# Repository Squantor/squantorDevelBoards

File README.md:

# Various development boards
This project contains a bunch of various development boards I use in my projects. They are usually focused on learning how to use a specific type of microcontroller or application.
## Nuclone development board series
As the name implies they resemble the [ST nucleo](https://www.st.com/en/evaluation-tools/stm32-nucleo-boards.html) in shape and function, minimal evaluation boards with all pins broken out and lot of jumpers.
## Structure
* [electronics](electronics/) contains the various nuclone examples, they are mostly [LPC microcontrollers](https://www.nxp.com/products/processors-and-microcontrollers/arm-microcontrollers/general-purpose-mcus:GENERAL-PURPOSE-MCUS) from [NXP](https://www.nxp.com/) but a few STM32's, nordic and holtek ARM microcontrollers are planned too.
* [software](software/) some example projects or project templates
* [mechanical](mechanical/) contains drawings for project boxes of the nuclone boards
## Checking out
This project makes extensive use of submodules, use ```git clone --recurse-submodules https://github.com/Squantor/squantorDevelBoards.git``` to clone the repository and its submodules in one go.

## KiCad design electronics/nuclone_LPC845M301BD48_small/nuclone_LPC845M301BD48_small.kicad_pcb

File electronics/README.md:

# Development board electronics
Stored here is the electronics for various development boards I use. Most are based on the "nuclone" principle. They look a lot like the STM32 nucleo series development boards.
## List of boards
* [nuclone board for the LPC804M101JHI33](nuclone_LPC804M101JHI33/README.md) is a breakout for the LPC804M101JHI33 microcontroller.
* [nuclone board for the LPC812M101JDH20](nuclone_LPC812M101JDH20/README.md) is a breakout for the LPC812M101JDH20 microcontroller.
* [nuclone board for the LPC824M201JDH20](nuclone_LPC824M201JDH20/README.md) is a breakout for the LPC824M201JDH20 microcontroller.
* [nuclone board for the LPC824M201JHI33](nuclone_LPC824M201JHI33/README.md) is a breakout for the LPC824M201JHI33 microcontroller.
* [nuclone board for the LPC844M201BD64](nuclone_LPC844M201BD64/README.md) is a breakout for the LPC844M201BD64 microcontroller.
* [nuclone board for the LPC845M301JBD48](nuclone_LPC845M301JBD48/README.md) is a breakout for the LPC845M301JBD48 microcontroller.
* [nuclone board for the LPC1114JBD48](nuclone_LPC1114JBD48/README.md) is a breakout for the LPC1114JBD48 microcontroller.
* [nuclone board for the LPC1125JBD48](nuclone_LPC1125JBD48/README.md) is a breakout for the LPC1125JBD48 microcontroller.
* [nuclone board for the STM32F030C8T6](nuclone_STM32F030C8T6/README.md) is a breakout for the STM32F030C8T6 microcontroller.
* [nuclone board for the STM32F030K6](nuclone_STM32F030K6/README.md) is a breakout for the STM32F030K6 microcontroller.
* [nuclone board for the STM32F031K6](nuclone_STM32F031K6/README.md) is a breakout for the STM32F031K6 microcontroller.
* [small nuclone universal expansion board with USB to UART and prototyping area](nuclone_small_uart_expansion/README.md).
* [LPC824M201JHI33 nuclone expansion board with SD card slot](nuclone_LPC824M201JHI33_expansion_microSD_card/README.md).
* [LPC824M201JHI33 nuclone expansion board with SOIC NOR Flash](nuclone_LPC824M201JHI33_expansion_serial_flash_SOIC/README.md).
* [LPC824M201JHI33 nuclone expansion board with USON NOR Flash](nuclone_LPC824M201JHI33_expansion_serial_flash_USON/README.md).
* [LPC824M201JHI33 nuclone expansion board with wearable prototyping circuit](nuclone_LPC824M201JHI33_expansion_wearable/README.md). This contains a battery charger, serial flash for datalogging, usb connection for data download and a few sensors like accelerometer, ambient light and a few more. (WIP)

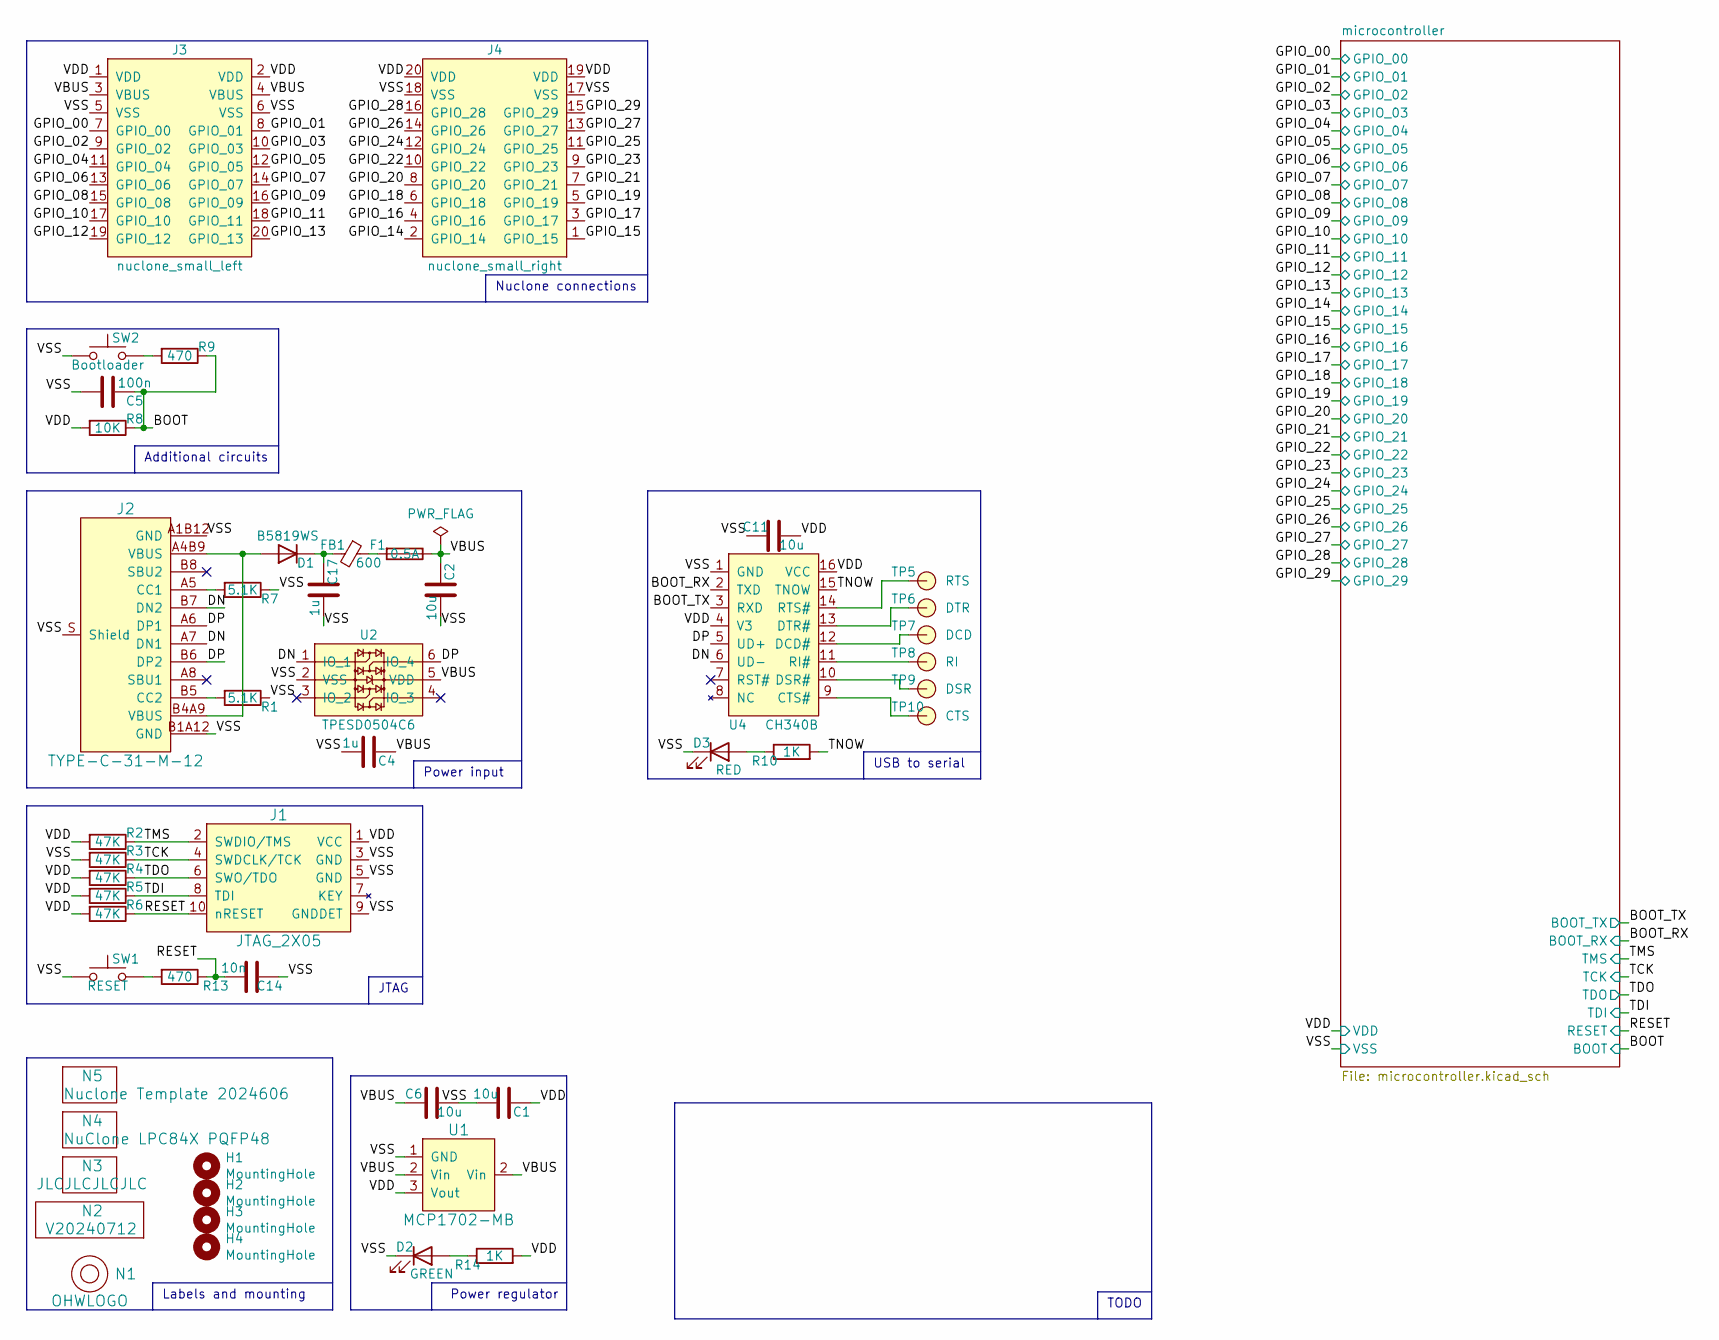
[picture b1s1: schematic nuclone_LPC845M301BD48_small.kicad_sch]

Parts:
C1, C2, C6, C11: 10u; C_0603
C4, C17: 1u; C_0603
C5: 100n; C_0603
C14: 10n; C_0603
D1: B5819WS; SOD-323-nexperia-hand
D2: GREEN; LED_0603_hand
D3: RED; LED_0603_hand
F1: 0.5A; F_0603_hand
FB1: 600; L_0603
H1, H2, H3, H4: MountingHole; MountingHole_3.2mm_M3_Pad_Via
J1: JTAG_2X05; Header-0127-2X05-H006
J2: TYPE-C-31-M-12; USB-C-HRO-31-M-12
J3: nuclone_small_left; nuclone_small_left_stacked
J4: nuclone_small_right; nuclone_small_right_stacked
N1: OHWLOGO; OSHW-Symbol_6.7x6mm_SilkScreen
N2: V20240712; Label_Generic
N3: JLCJLCJLCJLC; Label_Generic
N4: NuClone LPC84X PQFP48; Label_Generic
N5: Nuclone Template 2024606; Label_Generic
R1, R7: 5.1K; R_0603_hand
R2, R3, R4, R5, R6: 47K; R_0603_hand
R8: 10K; R_0603_hand
R9, R13: 470; R_0603_hand
R10, R14: 1K; R_0603_hand
SW1: RESET; TD-85XU
SW2: Bootloader; TD-85XU
TP5: RTS; TestPoint_hole_H05R10
TP6: DTR; TestPoint_hole_H05R10
TP7: DCD; TestPoint_hole_H05R10
TP8: RI; TestPoint_hole_H05R10
TP9: DSR; TestPoint_hole_H05R10
TP10: CTS; TestPoint_hole_H05R10
U1: MCP1702-MB; SOT89-NXP
U2: TPESD0504C6; SOT363-ONsemi
U4: CH340B; SOIC-16_3.9x9.9mm_P1.27mm

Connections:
/BOOT: C5.1, R8.1, R9.1; also elsewhere on the board
/BOOT_RX: U4.2 (TXD); also elsewhere on the board
/BOOT_TX: U4.3 (RXD); also elsewhere on the board
/DN: J2.A7 (DN1), J2.B7 (DN2), U2.1 (IO_1), U4.6 (UD-)
/DP: J2.A6 (DP1), J2.B6 (DP2), U2.6 (IO_4), U4.5 (UD+)
/GPIO_00: J3.7 (GPIO_00); also elsewhere on the board
/GPIO_01: J3.8 (GPIO_01); also elsewhere on the board
/GPIO_02: J3.9 (GPIO_02); also elsewhere on the board
/GPIO_03: J3.10 (GPIO_03); also elsewhere on the board
/GPIO_04: J3.11 (GPIO_04); also elsewhere on the board
/GPIO_05: J3.12 (GPIO_05); also elsewhere on the board
/GPIO_06: J3.13 (GPIO_06); also elsewhere on the board
/GPIO_07: J3.14 (GPIO_07); also elsewhere on the board
/GPIO_08: J3.15 (GPIO_08); also elsewhere on the board
/GPIO_09: J3.16 (GPIO_09); also elsewhere on the board
/GPIO_10: J3.17 (GPIO_10); also elsewhere on the board
/GPIO_11: J3.18 (GPIO_11); also elsewhere on the board
/GPIO_12: J3.19 (GPIO_12); also elsewhere on the board
/GPIO_13: J3.20 (GPIO_13); also elsewhere on the board
/GPIO_14: J4.2 (GPIO_14); also elsewhere on the board
/GPIO_15: J4.1 (GPIO_15); also elsewhere on the board
/GPIO_16: J4.4 (GPIO_16); also elsewhere on the board
/GPIO_17: J4.3 (GPIO_17); also elsewhere on the board
/GPIO_18: J4.6 (GPIO_18); also elsewhere on the board
/GPIO_19: J4.5 (GPIO_19); also elsewhere on the board
/GPIO_20: J4.8 (GPIO_20); also elsewhere on the board
/GPIO_21: J4.7 (GPIO_21); also elsewhere on the board
/GPIO_22: J4.10 (GPIO_22); also elsewhere on the board
/GPIO_23: J4.9 (GPIO_23); also elsewhere on the board
/GPIO_24: J4.12 (GPIO_24); also elsewhere on the board
/GPIO_25: J4.11 (GPIO_25); also elsewhere on the board
/GPIO_26: J4.14 (GPIO_26); also elsewhere on the board
/GPIO_27: J4.13 (GPIO_27); also elsewhere on the board
/GPIO_28: J4.16 (GPIO_28); also elsewhere on the board
/GPIO_29: J4.15 (GPIO_29); also elsewhere on the board
/RESET: C14.2, J1.10 (nRESET), R6.1, R13.1; also elsewhere on the board
/TCK: J1.4 (SWDCLK/TCK), R3.1; also elsewhere on the board
/TDI: J1.8 (TDI), R5.1
/TDO: J1.6 (SWO/TDO), R4.1
/TMS: J1.2 (SWDIO/TMS), R2.1; also elsewhere on the board
/TNOW: R10.2, U4.15 (TNOW)
/VBUS: C2.2, C4.1, C6.1, F1.1, J3.3 (VBUS), J3.4 (VBUS), U1.2 (Vin), U2.5 (VDD)
/VDD: C1.1, C11.1, J1.1 (VCC), J3.1 (VDD), J3.2 (VDD), J4.19 (VDD), J4.20 (VDD), R2.2, R4.2, R5.2, R6.2, R8.2, R14.2, U1.3 (Vout), U4.4 (V3), U4.16 (VCC); also elsewhere on the board
/VSS: C1.2, C2.1, C4.2, C5.2, C6.2, C11.2, C14.1, C17.1, D2.1 (K), D3.1 (K), J1.3 (GND), J1.5 (GND), J1.9 (GNDDET), J2.A1B12 (GND), J2.B1A12 (GND), J2.S (Shield), J3.5 (VSS), J3.6 (VSS), J4.17 (VSS), J4.18 (VSS), R1.1, R3.2, R7.1, SW1.1, SW2.1, U1.1 (GND), U2.2 (VSS), U4.1 (GND); also elsewhere on the board
unnamed: D1.2 (A), J2.A4B9 (VBUS), J2.B4A9 (VBUS)
unnamed: C17.2, D1.1 (K), FB1.2
unnamed: D2.2 (A), R14.1
unnamed: D3.2 (A), R10.1
unnamed: F1.2, FB1.1
unnamed: J2.A5 (CC1), R7.2
unnamed: J2.B5 (CC2), R1.2
unnamed: R9.2, SW2.2
unnamed: R13.2, SW1.2
unnamed: TP10.1, U4.9 (CTS#)
unnamed: TP7.1, U4.12 (DCD#)
unnamed: TP9.1, U4.10 (DSR#)
unnamed: TP6.1, U4.13 (DTR#)
unnamed: TP8.1, U4.11 (RI#)
unnamed: TP5.1, U4.14 (RTS#)

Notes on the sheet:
Power input
Nuclone connections
USB to serial
Additional circuits
TODO
Power regulator
Labels and mounting
JTAG

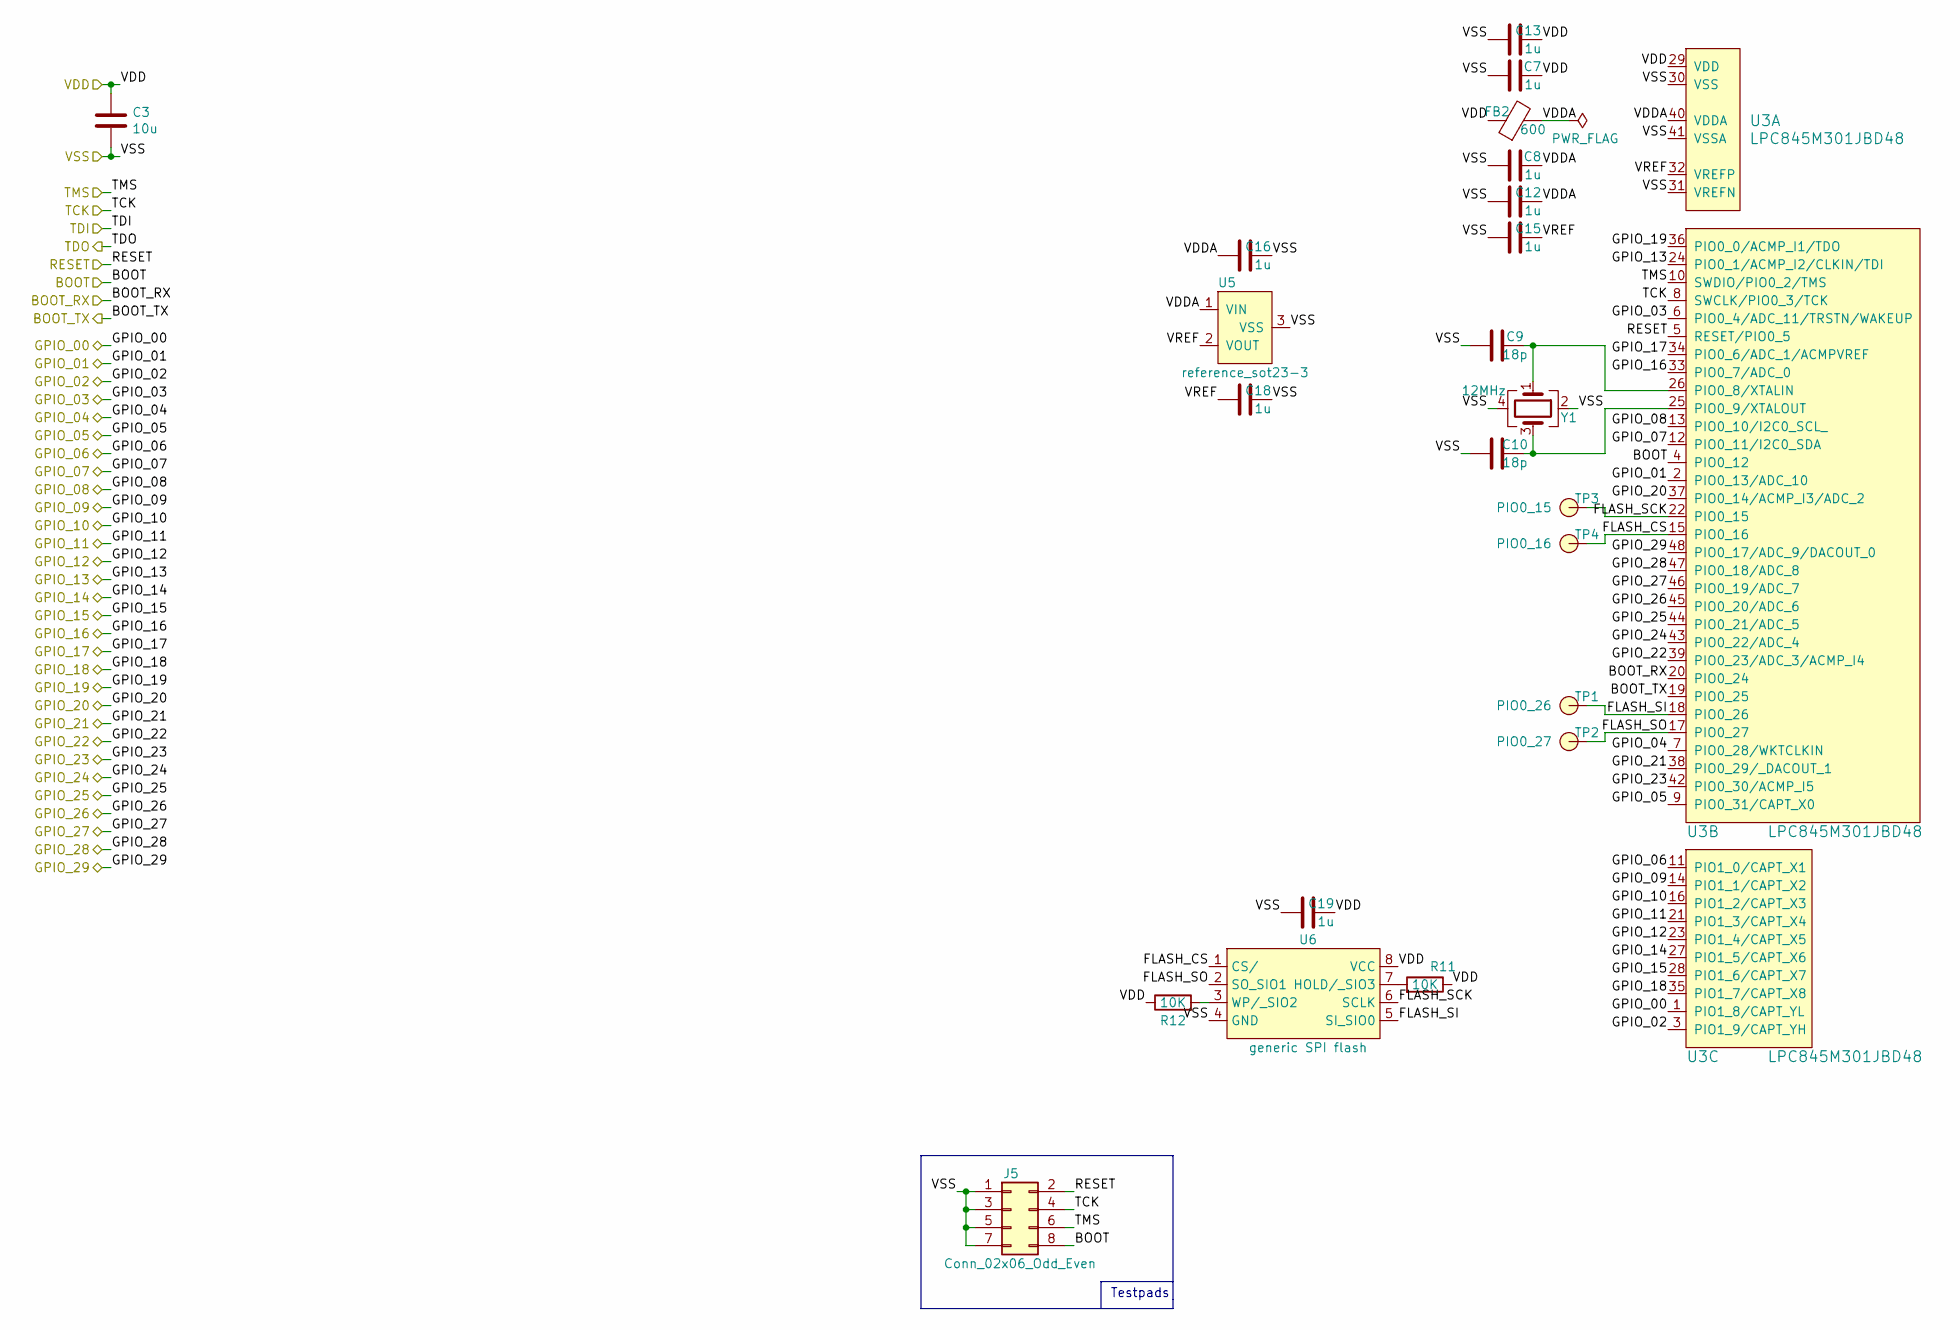
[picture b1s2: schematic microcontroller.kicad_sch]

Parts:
C3: 10u; C_0603
C7, C8, C16, C18, C19: 1u; C_0603
C9, C10: 18p; C_0603
C12, C13, C15: 1u; C_0402
FB2: 600; L_0603
J5: Conn_02x06_Odd_Even; Header-0127-2X04-H006
R11, R12: 10K; R_0603_hand
TP1: PIO0_26; TestPoint_hole_H05R10
TP2: PIO0_27; TestPoint_hole_H05R10
TP3: PIO0_15; TestPoint_hole_H05R10
TP4: PIO0_16; TestPoint_hole_H05R10
U3: LPC845M301JBD48; SOT313-2-NXP
U5: reference_sot23-3; SOT23-3
U6: generic SPI flash; SOIC-8_dual_wide
Y1: 12MHz; Crystal_3225_4_hand

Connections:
/BOOT: J5.8, U3.4 (PIO0_12); also elsewhere on the board
/BOOT_RX: U3.20 (PIO0_24); also elsewhere on the board
/BOOT_TX: U3.19 (PIO0_25); also elsewhere on the board
/GPIO_00: U3.1 (PIO1_8/CAPT_YL); also elsewhere on the board
/GPIO_01: U3.2 (PIO0_13/ADC_10); also elsewhere on the board
/GPIO_02: U3.3 (PIO1_9/CAPT_YH); also elsewhere on the board
/GPIO_03: U3.6 (PIO0_4/ADC_11/TRSTN/WAKEUP); also elsewhere on the board
/GPIO_04: U3.7 (PIO0_28/WKTCLKIN); also elsewhere on the board
/GPIO_05: U3.9 (PIO0_31/CAPT_X0); also elsewhere on the board
/GPIO_06: U3.11 (PIO1_0/CAPT_X1); also elsewhere on the board
/GPIO_07: U3.12 (PIO0_11/I2C0_SDA); also elsewhere on the board
/GPIO_08: U3.13 (PIO0_10/I2C0_SCL_); also elsewhere on the board
/GPIO_09: U3.14 (PIO1_1/CAPT_X2); also elsewhere on the board
/GPIO_10: U3.16 (PIO1_2/CAPT_X3); also elsewhere on the board
/GPIO_11: U3.21 (PIO1_3/CAPT_X4); also elsewhere on the board
/GPIO_12: U3.23 (PIO1_4/CAPT_X5); also elsewhere on the board
/GPIO_13: U3.24 (PIO0_1/ACMP_I2/CLKIN/TDI); also elsewhere on the board
/GPIO_14: U3.27 (PIO1_5/CAPT_X6); also elsewhere on the board
/GPIO_15: U3.28 (PIO1_6/CAPT_X7); also elsewhere on the board
/GPIO_16: U3.33 (PIO0_7/ADC_0); also elsewhere on the board
/GPIO_17: U3.34 (PIO0_6/ADC_1/ACMPVREF); also elsewhere on the board
/GPIO_18: U3.35 (PIO1_7/CAPT_X8); also elsewhere on the board
/GPIO_19: U3.36 (PIO0_0/ACMP_I1/TDO); also elsewhere on the board
/GPIO_20: U3.37 (PIO0_14/ACMP_I3/ADC_2); also elsewhere on the board
/GPIO_21: U3.38 (PIO0_29/_DACOUT_1); also elsewhere on the board
/GPIO_22: U3.39 (PIO0_23/ADC_3/ACMP_I4); also elsewhere on the board
/GPIO_23: U3.42 (PIO0_30/ACMP_I5); also elsewhere on the board
/GPIO_24: U3.43 (PIO0_22/ADC_4); also elsewhere on the board
/GPIO_25: U3.44 (PIO0_21/ADC_5); also elsewhere on the board
/GPIO_26: U3.45 (PIO0_20/ADC_6); also elsewhere on the board
/GPIO_27: U3.46 (PIO0_19/ADC_7); also elsewhere on the board
/GPIO_28: U3.47 (PIO0_18/ADC_8); also elsewhere on the board
/GPIO_29: U3.48 (PIO0_17/ADC_9/DACOUT_0); also elsewhere on the board
/RESET: J5.2, U3.5 (RESET/PIO0_5); also elsewhere on the board
/TCK: J5.4, U3.8 (SWCLK/PIO0_3/TCK); also elsewhere on the board
/TMS: J5.6, U3.10 (SWDIO/PIO0_2/TMS); also elsewhere on the board
/VDD: C3.1, C7.2, C13.2, C19.2, FB2.1, R11.1, R12.1, U3.29 (VDD), U6.8 (VCC); also elsewhere on the board
/VSS: C3.2, C7.1, C8.1, C9.2, C10.2, C12.1, C13.1, C15.1, C16.2, C18.2, C19.1, J5.1, J5.3, J5.5, J5.7, U3.30 (VSS), U3.31 (VREFN), U3.41 (VSSA), U5.3 (VSS), U6.4 (GND), Y1.2, Y1.4; also elsewhere on the board
/microcontroller/FLASH_CS: TP4.1, U3.15 (PIO0_16), U6.1 (CS/)
/microcontroller/FLASH_SCK: TP3.1, U3.22 (PIO0_15), U6.6 (SCLK)
/microcontroller/FLASH_SI: TP1.1, U3.18 (PIO0_26), U6.5 (SI_SIO0)
/microcontroller/FLASH_SO: TP2.1, U3.17 (PIO0_27), U6.2 (SO_SIO1)
/microcontroller/VDDA: C8.2, C12.2, C16.1, FB2.2, U3.40 (VDDA), U5.1 (VIN)
/microcontroller/VREF: C15.2, C18.1, U3.32 (VREFP), U5.2 (VOUT)
unnamed: C9.1, U3.26 (PIO0_8/XTALIN), Y1.1
unnamed: C10.1, U3.25 (PIO0_9/XTALOUT), Y1.3
unnamed: R11.2, U6.7 (HOLD/_SIO3)
unnamed: R12.2, U6.3 (WP/_SIO2)

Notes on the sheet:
Testpads

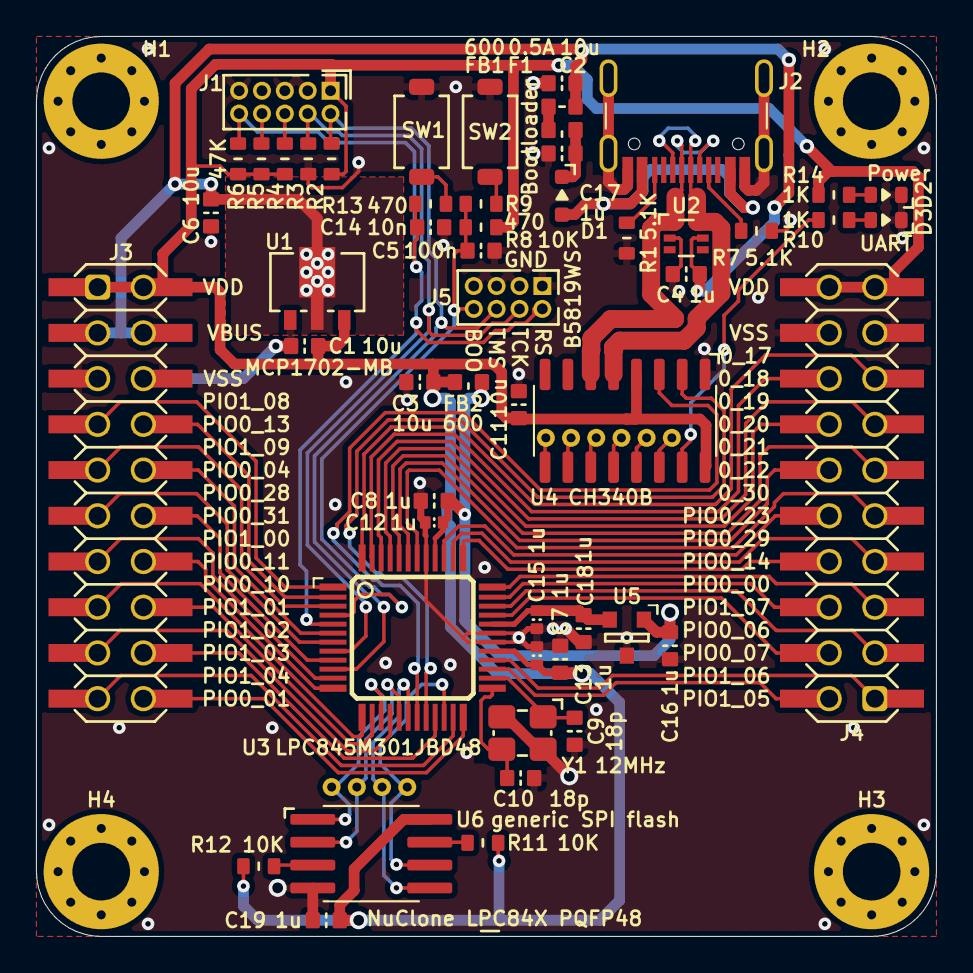
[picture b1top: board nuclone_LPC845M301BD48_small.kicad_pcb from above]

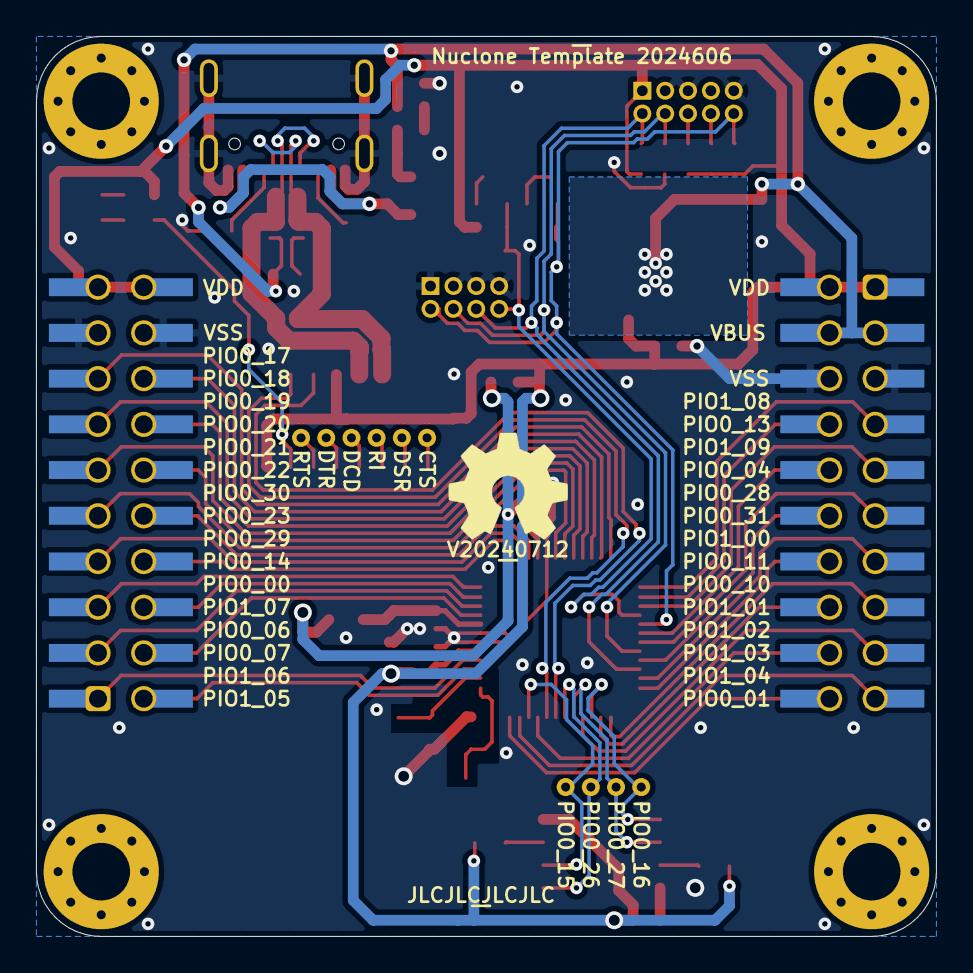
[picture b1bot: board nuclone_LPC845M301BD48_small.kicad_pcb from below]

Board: 2 copper layers, 50.0 x 50.0 mm, 72 parts (14 on the bottom side), 69 nets.

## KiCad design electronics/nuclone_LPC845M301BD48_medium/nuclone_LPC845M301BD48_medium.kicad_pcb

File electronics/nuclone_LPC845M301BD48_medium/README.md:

# medium nuclone board LPC845 PQFP48
Medium sized nuclone board LPC845 PQFP48
## TODO's
Still some things need to be done:
* schematic entry 
* PCB layout
* Review with one night in between
* Produce at [OSHPARK](https://oshpark.com/)
* Assemble
* Test & characterise
* update Readme.md with pictures and BOM
## BOM

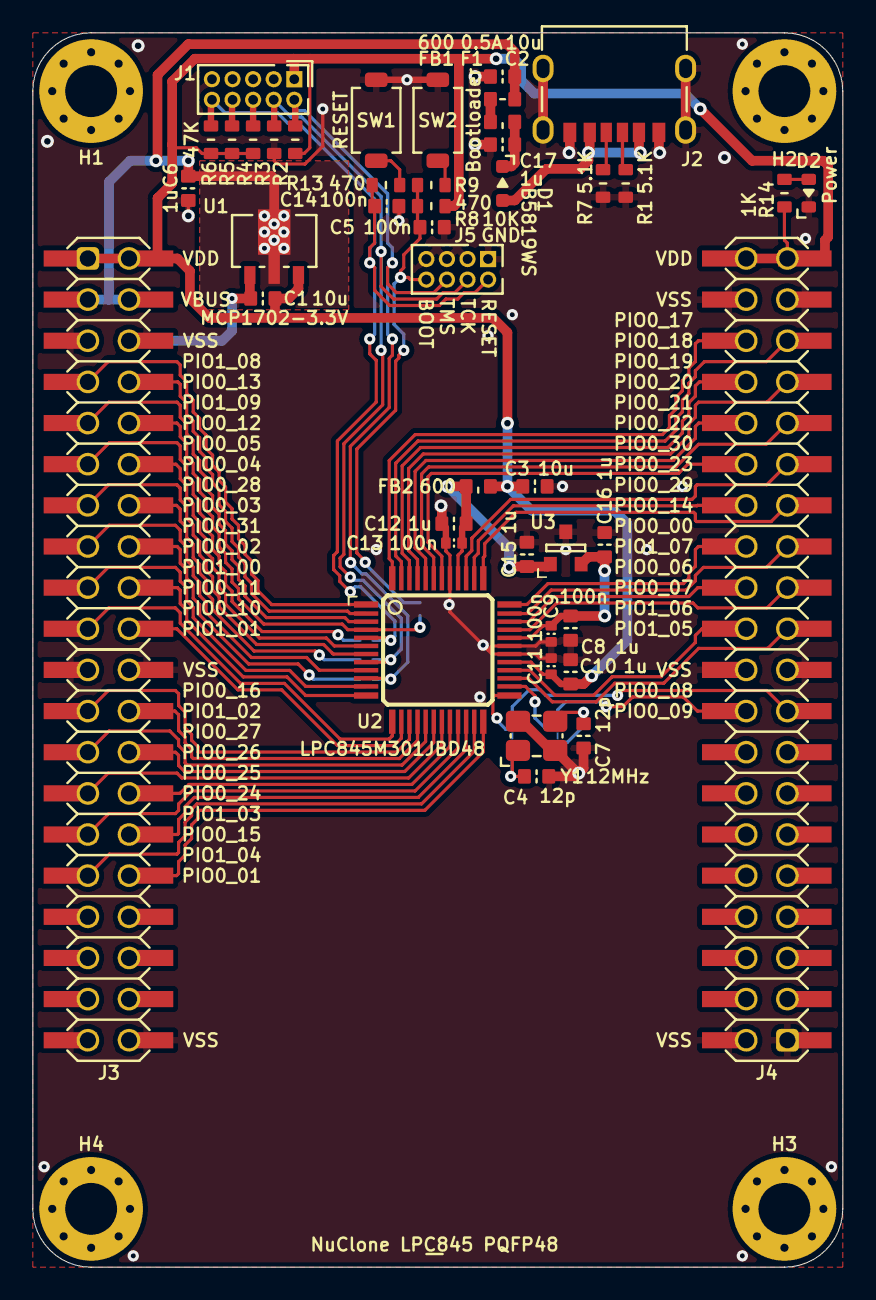
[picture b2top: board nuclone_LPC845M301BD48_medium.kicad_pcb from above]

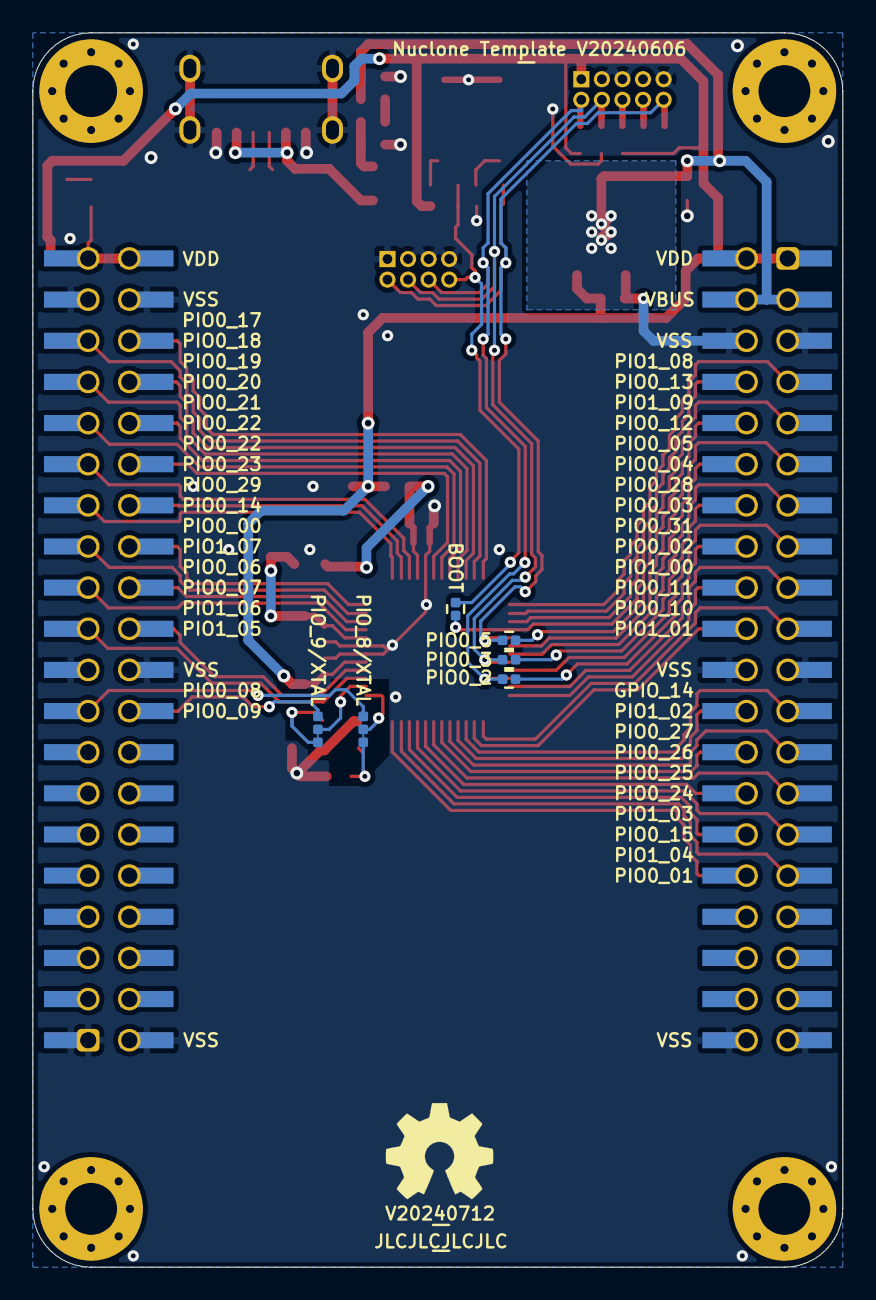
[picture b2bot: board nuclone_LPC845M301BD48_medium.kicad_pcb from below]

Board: 2 copper layers, 50.0 x 76.2 mm, 59 parts (10 on the bottom side), 65 nets.

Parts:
C1, C2, C3: 10u; C_0603
C4, C7: 12p; C_0603
C5, C14: 100n; C_0603
C6, C8, C10, C12, C15, C16, C17: 1u; C_0603
C9, C11, C13: 100n; C_0402
D1: B5819WS; SOD-323-nexperia-hand
D2: GREEN; LED_0603_hand
F1: 0.5A; F_0603_hand
FB1, FB2: 600; L_0603
H1, H2, H3, H4: MountingHole; MountingHole_3.2mm_M3_Pad_Via
J1: JTAG_2X05; Header-0127-2X05-H006
J2: TYPE-C-31-M-12; USB-C-HRO-31-M-17_aisler
J3: nuclone_medium_left; nuclone_medium_left_stacked
J4: nuclone_medium_right; nuclone_medium_right_stacked
J5: Conn_02x06_Odd_Even; Header-0127-2X04-H006
JP1: BOOT; solder_jumper_0402_2way_noconn
JP3: PIO0_2; solder_jumper_0402_2way_noconn
JP4: PIO0_3; solder_jumper_0402_2way_noconn
JP5: PIO0_5; solder_jumper_0402_2way_noconn
JP6: PIO_8/XTAL; solder_jumper_0402_3way_12conn
JP7: PIO_9/XTAL; solder_jumper_0402_3way_12conn
N1: OHWLOGO; OSHW-Symbol_6.7x6mm_SilkScreen
N2: V20240712; Label_Generic
N3: JLCJLCJLCJLC; Label_Generic
N4: NuClone LPC845 PQFP48; Label_Generic
N5: Nuclone Template V20240606; Label_Generic
R1, R7: 5.1K; R_0603_hand
R2, R3, R4, R5, R6: 47K; R_0603_hand
R8: 10K; R_0603_hand
R9, R13: 470; R_0603_hand
R14: 1K; R_0603_hand
SW1: RESET; TD-85XU
SW2: Bootloader; TD-85XU
U1: MCP1702-3.3V; SOT89-NXP
U2: LPC845M301JBD48; SOT313-2-NXP
U3: reference_sot23-3; SOT23-3
Y1: 12MHz; Crystal_3225_4_hand

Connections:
/Bootloader: C5.1, J5.8, JP1.2, R8.1, R9.1
/GPIO_00: J3.7 (GPIO_00), U2.1 (PIO1_8/CAPT_YL)
/GPIO_01: J3.8 (GPIO_01), U2.2 (PIO0_13/ADC_10)
/GPIO_02: J3.9 (GPIO_02), U2.3 (PIO1_9/CAPT_YH)
/GPIO_03: J3.10 (GPIO_03), JP1.1, U2.4 (PIO0_12)
/GPIO_04: J3.11 (GPIO_04), JP5.1
/GPIO_05: J3.12 (GPIO_05), U2.6 (PIO0_4/ADC_11/TRSTN/WAKEUP)
/GPIO_06: J3.13 (GPIO_06), U2.7 (PIO0_28/WKTCLKIN)
/GPIO_07: J3.14 (GPIO_07), JP4.1
/GPIO_08: J3.15 (GPIO_08), U2.9 (PIO0_31/CAPT_X0)
/GPIO_09: J3.16 (GPIO_09), JP3.1
/GPIO_10: J3.17 (GPIO_10), U2.11 (PIO1_0/CAPT_X1)
/GPIO_11: J3.18 (GPIO_11), U2.12 (PIO0_11/I2C0_SDA)
/GPIO_12: J3.19 (GPIO_12), U2.13 (PIO0_10/I2C0_SCL_)
/GPIO_13: J3.20 (GPIO_13), U2.14 (PIO1_1/CAPT_X2)
/GPIO_14: J3.23 (GPIO_14), U2.15 (PIO0_16)
/GPIO_15: J3.24 (GPIO_15), U2.16 (PIO1_2/CAPT_X3)
/GPIO_16: J3.25 (GPIO_16), U2.17 (PIO0_27)
/GPIO_17: J3.26 (GPIO_17), U2.18 (PIO0_26)
/GPIO_18: J3.27 (GPIO_18), U2.19 (PIO0_25)
/GPIO_19: J3.28 (GPIO_19), U2.20 (PIO0_24)
/GPIO_20: J3.29 (GPIO_20), U2.21 (PIO1_3/CAPT_X4)
/GPIO_21: J3.30 (GPIO_21), U2.22 (PIO0_15)
/GPIO_22: J3.31 (GPIO_22), U2.23 (PIO1_4/CAPT_X5)
/GPIO_23: J3.32 (GPIO_23), U2.24 (PIO0_1/ACMP_I2/CLKIN/TDI)
/GPIO_44: J4.17 (GPIO_45), JP6.3
/GPIO_45: J4.18 (GPIO_44), JP7.3
/GPIO_46: J4.21 (GPIO_47), U2.27 (PIO1_5/CAPT_X6)
/GPIO_47: J4.22 (GPIO_46), U2.28 (PIO1_6/CAPT_X7)
/GPIO_48: J4.23 (GPIO_49), U2.33 (PIO0_7/ADC_0)
/GPIO_49: J4.24 (GPIO_48), U2.34 (PIO0_6/ADC_1/ACMPVREF)
/GPIO_50: J4.25 (GPIO_51), U2.35 (PIO1_7/CAPT_X8)
/GPIO_51: J4.26 (GPIO_50), U2.36 (PIO0_0/ACMP_I1/TDO)
/GPIO_52: J4.27 (GPIO_53), U2.37 (PIO0_14/ACMP_I3/ADC_2)
/GPIO_53: J4.28 (GPIO_52), U2.38 (PIO0_29/_DACOUT_1)
/GPIO_54: J4.29 (GPIO_55), U2.39 (PIO0_23/ADC_3/ACMP_I4)
/GPIO_55: J4.30 (GPIO_54), U2.42 (PIO0_30/ACMP_I5)
/GPIO_56: J4.31 (GPIO_57), U2.43 (PIO0_22/ADC_4)
/GPIO_57: J4.32 (GPIO_56), U2.44 (PIO0_21/ADC_5)
/GPIO_58: J4.33 (GPIO_59), U2.45 (PIO0_20/ADC_6)
/GPIO_59: J4.34 (GPIO_58), U2.46 (PIO0_19/ADC_7)
/GPIO_60: J4.35 (GPIO_61), U2.47 (PIO0_18/ADC_8)
/GPIO_61: J4.36 (GPIO_60), U2.48 (PIO0_17/ADC_9/DACOUT_0)
/RESET: C14.2, J1.10 (nRESET), J5.2, JP5.2, R6.1, R13.1, U2.5 (RESET/PIO0_5)
/TCK: J1.4 (SWDCLK/TCK), J5.4, JP4.2, R3.1, U2.8 (SWCLK/PIO0_3/TCK)
/TDI: J1.8 (TDI), R5.1
/TDO: J1.6 (SWO/TDO), R4.1
/TMS: J1.2 (SWDIO/TMS), J5.6, JP3.2, R2.1, U2.10 (SWDIO/PIO0_2/TMS)
/VBUS: C2.2, C6.2, F1.1, J3.3 (VBUS), J3.4 (VBUS), U1.2 (Vin)
/VDD: C1.1, C3.2, C10.1, C11.1, FB2.2, J1.1 (VCC), J3.1 (VDD), J3.2 (VDD), J4.39 (VDD), J4.40 (VDD), R2.2, R4.2, R5.2, R6.2, R8.2, R14.2, U1.3 (Vout), U2.29 (VDD)
/VSS: C1.2, C2.1, C3.1, C4.2, C5.2, C6.1, C7.2, C8.2, C9.2, C10.2, C11.2, C12.2, C13.2, C14.1, C15.2, C16.2, C17.1, D2.1 (K), J1.3 (GND), J1.5 (GND), J1.9 (GNDDET), J2.A12 (GND), J2.B12 (GND), J2.S (Shield), J3.5 (VSS), J3.6 (VSS), J3.21 (VSS), J3.22 (VSS), J3.39 (VSS), J3.40 (VSS), J4.1 (VSS), J4.2 (VSS), J4.19 (VSS), J4.20 (VSS), J4.37 (VSS), J4.38 (VSS), J5.1, J5.3, J5.5, J5.7, R1.1, R3.2, R7.1, SW1.1, SW2.1, U1.1 (GND), U2.30 (VSS), U2.31 (VREFN), U2.41 (VSSA), U3.3 (VSS), Y1.2, Y1.4
/VUSB: D1.2 (A), J2.A9 (VBUS), J2.B9 (VBUS)
/microcontroller/PIO0_8_I: JP7.2, U2.26 (PIO0_8/XTALIN)
/microcontroller/PIO0_9_I: JP6.2, U2.25 (PIO0_9/XTALOUT)
/microcontroller/VDDA: C12.1, C13.1, C15.1, FB2.1, U2.40 (VDDA), U3.1 (VIN)
/microcontroller/VREFP: C8.1, C9.1, C16.1, U2.32 (VREFP), U3.2 (VOUT)
/microcontroller/XTALIN: C4.1, JP6.1, Y1.1
/microcontroller/XTALOUT: C7.1, JP7.1, Y1.3
unnamed: C17.2, D1.1 (K), FB1.2
unnamed: D2.2 (A), R14.1
unnamed: F1.2, FB1.1
unnamed: J2.A5 (CC1), R1.2
unnamed: J2.B5 (CC2), R7.2
unnamed: R9.2, SW2.2
unnamed: R13.2, SW1.2

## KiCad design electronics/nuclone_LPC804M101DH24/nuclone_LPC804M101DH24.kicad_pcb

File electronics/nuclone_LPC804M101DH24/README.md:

# Nuclone microcontroller board with LPC804 TSSOP24
Nuclone board 
# HSI (Hardware Software Interface)
TODO: Voltage reference
## TODO's
Still some things need to be done:
* PCB layout
* Review with one night in between
* Produce at [OSHPARK](https://oshpark.com/)
* Assemble
* Test & characterise
* update Readme.md with pictures and BOM
## BOM
* LPC804M101DH24
## Pictures

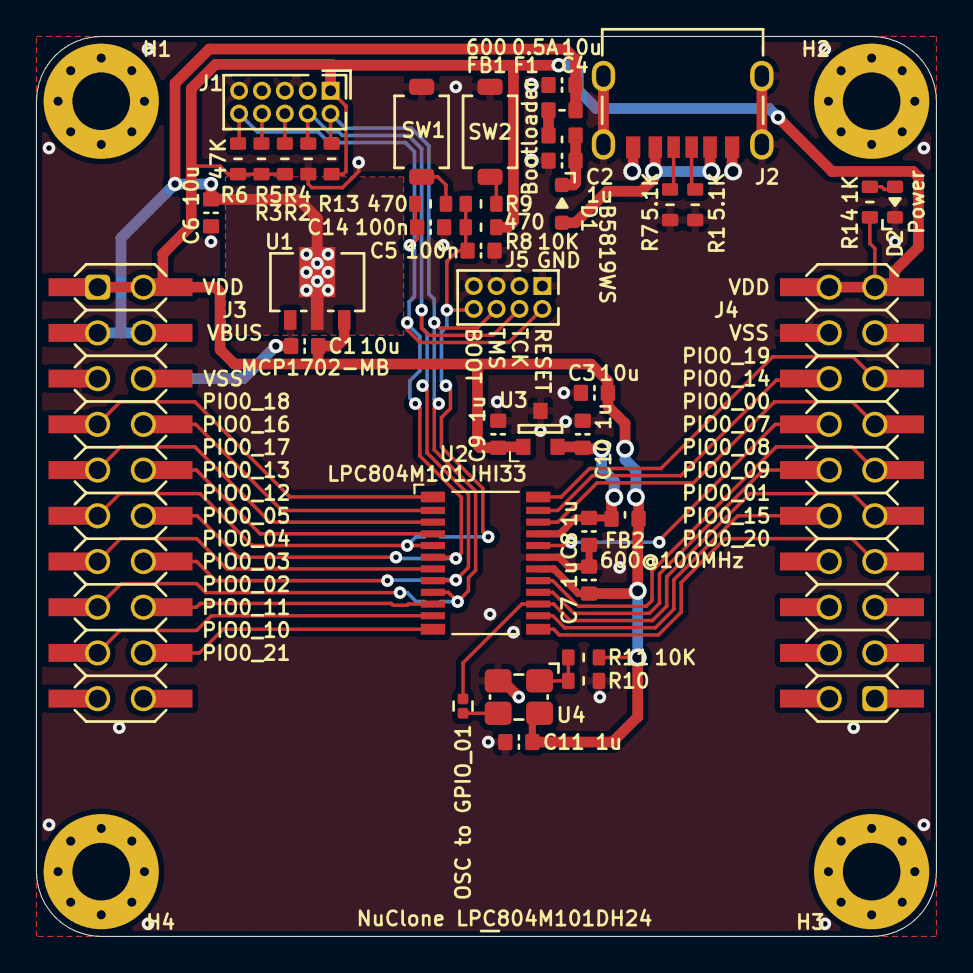
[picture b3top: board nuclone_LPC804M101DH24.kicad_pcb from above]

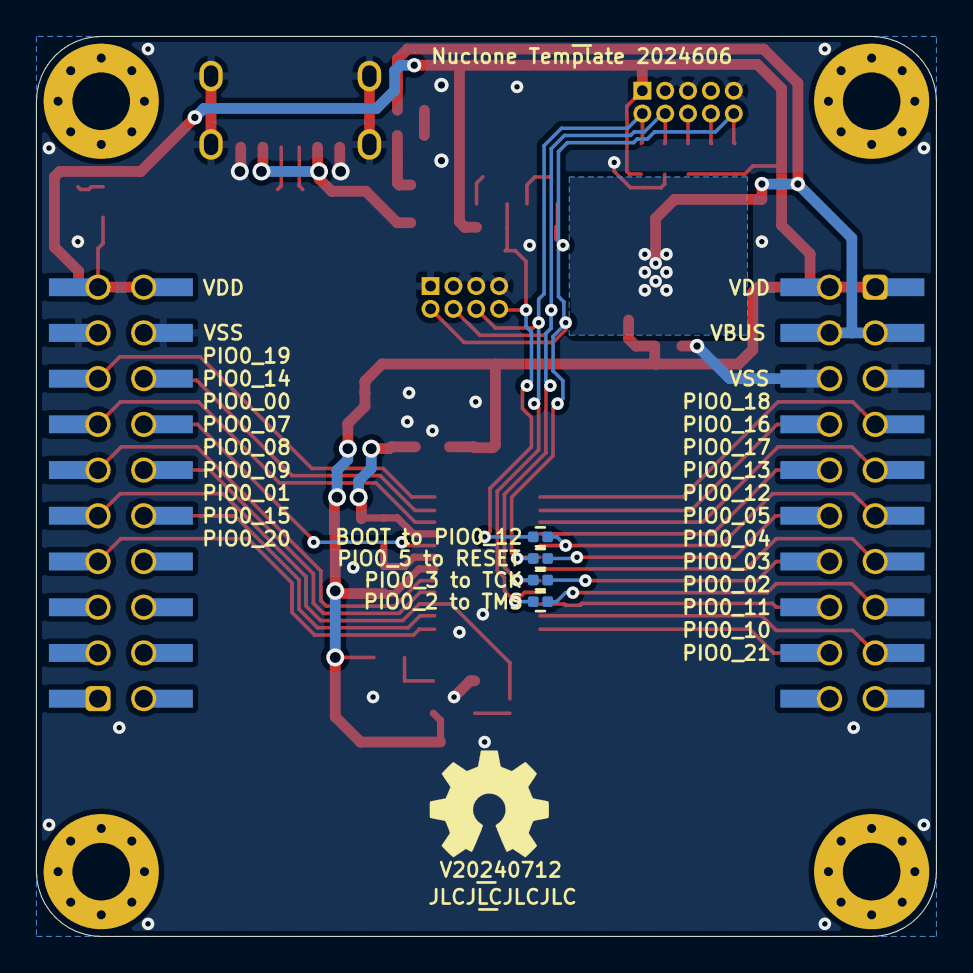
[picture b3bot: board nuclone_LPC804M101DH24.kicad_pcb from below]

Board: 2 copper layers, 50.0 x 50.0 mm, 55 parts (8 on the bottom side), 41 nets.

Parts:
C1, C3, C4, C6: 10u; C_0603
C2, C7, C8, C9, C10, C11: 1u; C_0603
C5, C14: 100n; C_0603
D1: B5819WS; SOD-323-nexperia-hand
D2: GREEN; LED_0603_hand
F1: 0.5A; F_0603_hand
FB1: 600; L_0603
FB2: 600@100MHz; L_0603
H1, H2, H3, H4: MountingHole; MountingHole_3.2mm_M3_Pad_Via
J1: JTAG_2X05; Header-0127-2X05-H006
J2: TYPE-C-31-M-12; USB-C-HRO-31-M-17_aisler
J3: nuclone_small_left; nuclone_small_left_stacked
J4: nuclone_small_right; nuclone_small_right_stacked
J5: Conn_02x06_Odd_Even; Header-0127-2X04-H006
JP1: PIO0_5 to RESET; solder_jumper_0402_2way_noconn
JP2: PIO0_3 to TCK; solder_jumper_0402_2way_noconn
JP3: PIO0_2 to TMS; solder_jumper_0402_2way_noconn
JP4: BOOT to PIO0_12; solder_jumper_0402_2way_noconn
JP5: OSC to GPIO_01; solder_jumper_0402_2way_noconn
N1: OHWLOGO; OSHW-Symbol_6.7x6mm_SilkScreen
N2: V20240712; Label_Generic
N3: JLCJLCJLCJLC; Label_Generic
N4: NuClone LPC804M101DH24; Label_Generic
N5: Nuclone Template 2024606; Label_Generic
R1, R7: 5.1K; R_0603_hand
R2, R3, R4, R5, R6: 47K; R_0603_hand
R8, R10, R11: 10K; R_0603_hand
R9, R13: 470; R_0603_hand
R14: 1K; R_0603_hand
SW1: RESET; TD-85XU
SW2: Bootloader; TD-85XU
U1: MCP1702-MB; SOT89-NXP
U2: LPC804M101JHI33; SOT355-1-NXP
U3: reference_sot23-3; SOT23-3
U4: TBD; Crystal_3225_4_hand

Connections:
/BOOT: C5.1, J5.8, JP4.1, R8.1, R9.1
/GPIO_00: J3.7 (GPIO_00), U2.1 (PIO0_18)
/GPIO_01: J3.8 (GPIO_01), U2.2 (PIO0_16/ADC_3/ACMP_I4)
/GPIO_02: J3.9 (GPIO_02), U2.3 (PIO0_17/ADC_9)
/GPIO_03: J3.10 (GPIO_03), U2.4 (PIO0_13/ADC_10)
/GPIO_04: J3.11 (GPIO_04), JP4.2, U2.5 (PIO0_12)
/GPIO_05: J3.12 (GPIO_05), JP1.1
/GPIO_06: J3.13 (GPIO_06), U2.7 (PIO0_4/ADC_11/TRSTN)
/GPIO_07: J3.14 (GPIO_07), JP2.1
/GPIO_08: J3.15 (GPIO_08), JP3.1
/GPIO_09: J3.16 (GPIO_09), U2.10 (PIO0_11/ADC_6/WKTCLKIN)
/GPIO_10: J3.17 (GPIO_10), U2.11 (PIO0_10/ADC_7)
/GPIO_11: J3.18 (GPIO_11), U2.12 (PIO0_21/ACMP_I5)
/GPIO_21: J4.7 (GPIO_21), U2.13 (PIO0_20)
/GPIO_22: J4.10 (GPIO_22), U2.14 (PIO0_15/ADC_8)
/GPIO_23: J4.9 (GPIO_23), JP5.2, U2.15 (PIO0_1/ADC_0/ACMP_I2/TDI/CLKIN)
/GPIO_24: J4.12 (GPIO_24), U2.16 (PIO0_9/ADC_4)
/GPIO_25: J4.11 (GPIO_25), U2.17 (PIO0_8/ADC_5)
/GPIO_26: J4.14 (GPIO_26), U2.20 (PIO0_7/ADC_1/ACMPVREF)
/GPIO_27: J4.13 (GPIO_27), U2.22 (PIO0_0/ACMP_I1/TDO)
/GPIO_28: J4.16 (GPIO_28), U2.23 (PIO0_14/ADC_2/ACMP_I3)
/GPIO_29: J4.15 (GPIO_29), U2.24 (PIO0_19/DACOUT)
/RESET: C14.2, J1.10 (nRESET), J5.2, JP1.2, R6.1, R13.1, U2.6 (!RESET/PIO0_5)
/TCK: J1.4 (SWDCLK/TCK), J5.4, JP2.2, R3.1, U2.8 (SWCLK/PIO0_3/TCK)
/TDI: J1.8 (TDI), R5.1
/TDO: J1.6 (SWO/TDO), R4.1
/TMS: J1.2 (SWDIO/TMS), J5.6, JP3.2, R2.1, U2.9 (SWDIO/PIO0_2/TMS)
/VBUS: C4.2, C6.1, F1.1, J3.3 (VBUS), J3.4 (VBUS), U1.2 (Vin)
/VDD: C1.1, C3.1, C7.2, C9.2, C11.2, FB2.1, J1.1 (VCC), J3.1 (VDD), J3.2 (VDD), J4.19 (VDD), J4.20 (VDD), R2.2, R4.2, R5.2, R6.2, R8.2, R11.2, R14.2, U1.3 (Vout), U2.18 (VDD), U3.1 (VIN), U4.4 (VDD)
/VSS: C1.2, C2.1, C3.2, C4.1, C5.2, C6.2, C7.1, C8.1, C9.1, C10.1, C11.1, C14.1, D2.1 (K), J1.3 (GND), J1.5 (GND), J1.9 (GNDDET), J2.A12 (GND), J2.B12 (GND), J2.S (Shield), J3.5 (VSS), J3.6 (VSS), J4.17 (VSS), J4.18 (VSS), J5.1, J5.3, J5.5, J5.7, R1.1, R3.2, R7.1, R10.2, SW1.1, SW2.1, U1.1 (GND), U2.19 (VSS), U3.3 (VSS), U4.2 (GND)
/VUSB: D1.2 (A), J2.A9 (VBUS), J2.B9 (VBUS)
/microcontroller/OSC_EN: R10.1, R11.1, U4.1 (Tri)
/microcontroller/OSC_OUT: JP5.1, U4.3 (OUT)
/microcontroller/VREFP: C8.2, C10.2, FB2.2, U2.21 (VREFP), U3.2 (VOUT)
unnamed: C2.2, D1.1 (K), FB1.2
unnamed: D2.2 (A), R14.1
unnamed: F1.2, FB1.1
unnamed: J2.A5 (CC1), R1.2
unnamed: J2.B5 (CC2), R7.2
unnamed: R9.2, SW2.2
unnamed: R13.2, SW1.2
